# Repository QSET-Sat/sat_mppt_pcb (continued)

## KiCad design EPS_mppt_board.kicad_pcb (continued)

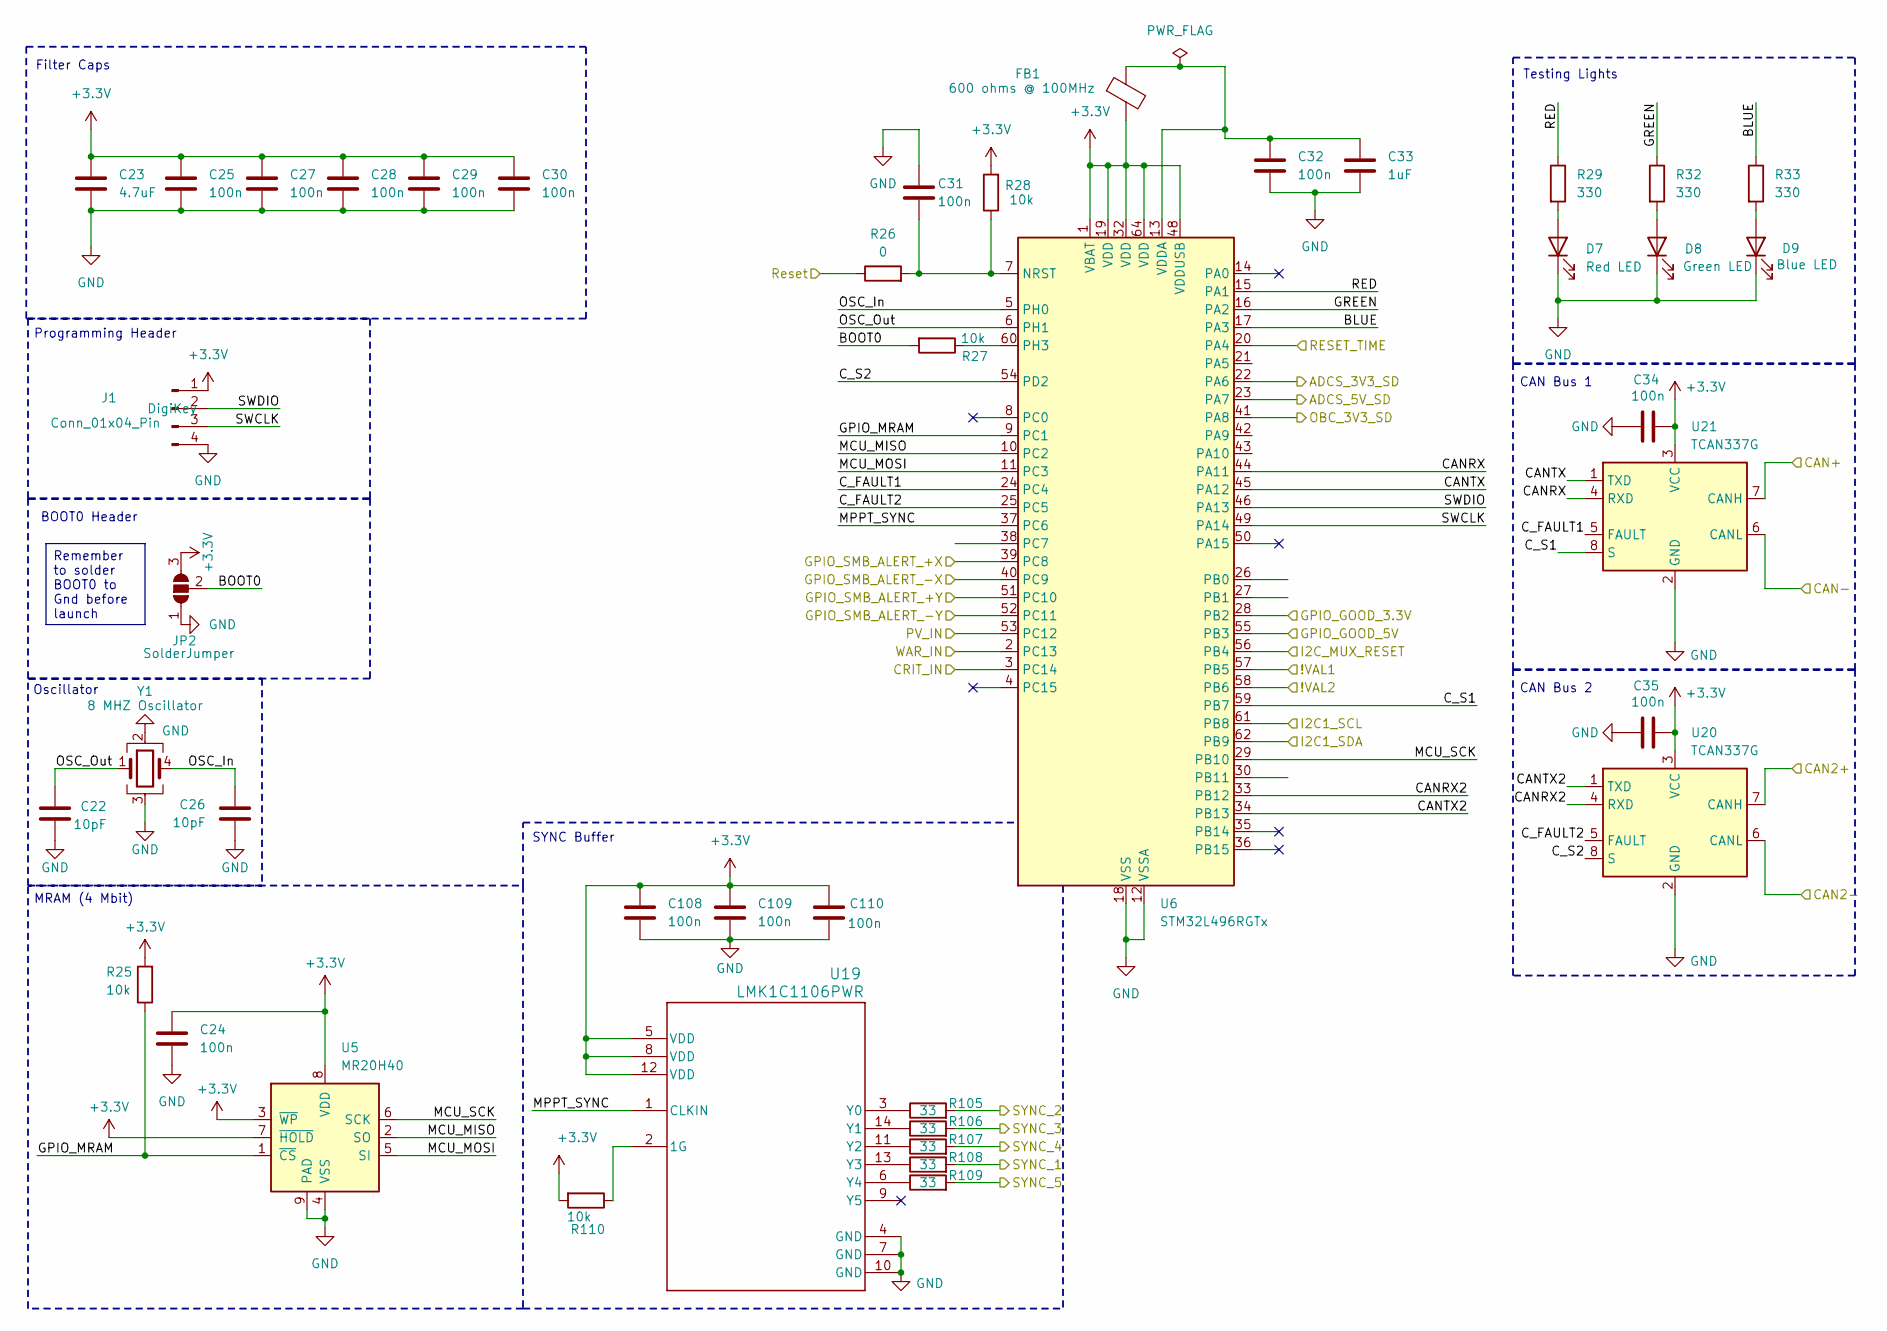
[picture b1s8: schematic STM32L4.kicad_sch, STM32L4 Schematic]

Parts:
C22, C26: 10pF; C_0603_1608Metric; MANUFACTURER_PART_NUMBER 06035C100K4T4A
C23: 4.7uF; C_0603_1608Metric; MANUFACTURER_PART_NUMBER CL10B475KQ8NQNC
C24, C25, C27, C28, C29, C30, C31, C32, C34, C35, C108, C109, C110: 100n; C_0603_1608Metric; MANUFACTURER_PART_NUMBER C0603X104K5RACTU
C33: 1uF; C_0603_1608Metric; MANUFACTURER_PART_NUMBER CL10B105KQ8NNNC
D7: Red LED; LED_0603_1608Metric; MANUFACTURER_PART_NUMBER 150060RS55040
D8: Green LED; LED_0603_1608Metric; MANUFACTURER_PART_NUMBER 150060VS55040
D9: Blue LED; LED_0603_1608Metric; MANUFACTURER_PART_NUMBER 150060BS55040
FB1: 600 ohms @ 100MHz; L_0603_1608Metric; MANUFACTURER_PART_NUMBER BLM18AG601SN1D
J1: Conn_01x04_Pin; JST_EH_B4B-EH-A_1x04_P2.50mm_Vertical
JP2: SolderJumper; SolderJumper-3_P1.3mm_Open_RoundedPad1.0x1.5mm_NumberLabels
R25, R27, R28: 10k; R_0805_2012Metric; MANUFACTURER_PART_NUMBER TNPW080510K0FEEA
R26: 0; R_0603_1608Metric; MANUFACTURER_PART_NUMBER MCT0603MZ0000ZP500
R29, R32, R33: 330; R_0603_1608Metric; MANUFACTURER_PART_NUMBER RG1608P-331-B-T5
R105, R106, R107, R108, R109: 33; R_0402_1005Metric
R110: 10k; R_0603_1608Metric
U5: MR20H40; DFN-8-1EP_6x5mm_P1.27mm_EP4x4mm
U6: STM32L496RGTx; LQFP-64_10x10mm_P0.5mm
U19: LMK1C1106PWR; PW0014A-IPC_B
U20, U21: TCAN337G; SOIC-8_3.9x4.9mm_P1.27mm
Y1: 8 MHZ Oscillator; Crystal_SMD_3225-4Pin_3.2x2.5mm

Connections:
+3.3V: C23.1, C24.2, C25.1, C27.1, C28.1, C29.1, C30.1, C34.2, C35.2, C108.1, C109.1, C110.1, FB1.2, J1.1, JP2.3 (B), R25.2, R28.2, R110.2, U5.3 (~WP), U5.7 (~HOLD), U5.8 (VDD), U6.1 (VBAT), U6.19 (VDD), U6.32 (VDD), U6.48 (VDDUSB), U6.64 (VDD), U19.5 (VDD), U19.8 (VDD), U19.12 (VDD), U20.3 (VCC), U21.3 (VCC); also elsewhere on the board
/3.3V and 5V Line/PGOOD1: U6.55 (PB3); also elsewhere on the board
/3.3V and 5V Line/PGOOD2: U6.28 (PB2); also elsewhere on the board
/3.3V and 5V Line/SYNC: R109.2; also elsewhere on the board
/Current Sensing and Fault Detection/ADCS_3V3_ShutDown: U6.22 (PA6); also elsewhere on the board
/Current Sensing and Fault Detection/ADCS_5V_ShutDown: U6.23 (PA7); also elsewhere on the board
/Current Sensing and Fault Detection/CRIT_INA3221: U6.3 (PC14); also elsewhere on the board
/Current Sensing and Fault Detection/OBC_3V3_ShutDown: U6.41 (PA8); also elsewhere on the board
/Current Sensing and Fault Detection/PV_INA3221: U6.53 (PC12); also elsewhere on the board
/Current Sensing and Fault Detection/SCL_INA3221: U6.61 (PB8); also elsewhere on the board
/Current Sensing and Fault Detection/SDA_INA3221: U6.62 (PB9); also elsewhere on the board
/Current Sensing and Fault Detection/WAR_INA3221: U6.2 (PC13); also elsewhere on the board
/EPS Logic/!VAL1: U6.57 (PB5); also elsewhere on the board
/EPS Logic/!VAL2: U6.58 (PB6); also elsewhere on the board
/External Watchdog IC/RESET_TIME: U6.20 (PA4); also elsewhere on the board
/External Watchdog IC/Reset: R26.1; also elsewhere on the board
/I2C Mux/I2C_Reset: U6.56 (PB4); also elsewhere on the board
/MPPT IC/!SMB_ALERT_+X: U6.39 (PC8); also elsewhere on the board
/MPPT IC/!SMB_ALERT_+Y: U6.51 (PC10); also elsewhere on the board
/MPPT IC/!SMB_ALERT_-X: U6.40 (PC9); also elsewhere on the board
/MPPT IC/!SMB_ALERT_-Y: U6.52 (PC11); also elsewhere on the board
/MPPT IC/MPPT_SYNC_1.5MHz_1: R108.2; also elsewhere on the board
/MPPT IC/MPPT_SYNC_1.5MHz_2: R105.2; also elsewhere on the board
/MPPT IC/MPPT_SYNC_1.5MHz_3: R106.2; also elsewhere on the board
/MPPT IC/MPPT_SYNC_1.5MHz_4: R107.2; also elsewhere on the board
/PC104/CAN2+: U20.7 (CANH); also elsewhere on the board
/PC104/CAN2-: U20.6 (CANL); also elsewhere on the board
/PC104/CAN+: U21.7 (CANH); also elsewhere on the board
/PC104/CAN-: U21.6 (CANL); also elsewhere on the board
/STM32L4/BLUE: R33.1, U6.17 (PA3)
/STM32L4/BOOT0: JP2.2 (C), R27.2
/STM32L4/CANRX: U6.44 (PA11), U21.4 (RXD)
/STM32L4/CANRX2: U6.33 (PB12), U20.4 (RXD)
/STM32L4/CANTX: U6.45 (PA12), U21.1 (TXD)
/STM32L4/CANTX2: U6.34 (PB13), U20.1 (TXD)
/STM32L4/C_FAULT1: U6.24 (PC4), U21.5 (FAULT)
/STM32L4/C_FAULT2: U6.25 (PC5), U20.5 (FAULT)
/STM32L4/C_S1: U6.59 (PB7), U21.8 (S)
/STM32L4/C_S2: U6.54 (PD2), U20.8 (S)
/STM32L4/GPIO_MRAM: R25.1, U5.1 (~CS), U6.9 (PC1)
/STM32L4/GREEN: R32.1, U6.16 (PA2)
/STM32L4/MCU_MISO: U5.2 (SO), U6.10 (PC2)
/STM32L4/MCU_MOSI: U5.5 (SI), U6.11 (PC3)
/STM32L4/MCU_SCK: U5.6 (SCK), U6.29 (PB10)
/STM32L4/MPPT_SYNC: U6.37 (PC6), U19.1 (CLKIN)
/STM32L4/OSC_In: C26.1, U6.5 (PH0), Y1.4
/STM32L4/OSC_Out: C22.1, U6.6 (PH1), Y1.1
/STM32L4/RED: R29.1, U6.15 (PA1)
/STM32L4/SWCLK: J1.3, U6.49 (PA14)
/STM32L4/SWDIO: J1.2, U6.46 (PA13)
unnamed: D7.2 (A), R29.2
unnamed: D8.2 (A), R32.2
unnamed: D9.2 (A), R33.2
unnamed: C31.2, R26.2, R28.1, U6.7 (NRST)
unnamed: R27.1, U6.60 (PH3)
unnamed: C32.1, C33.1, FB1.1, U6.13 (VDDA)
unnamed: R110.1, U19.2 (1G)
unnamed: R105.1, U19.3 (Y0)
unnamed: R106.1, U19.14 (Y1)
unnamed: R107.1, U19.11 (Y2)
unnamed: R108.1, U19.13 (Y3)
unnamed: R109.1, U19.6 (Y4)

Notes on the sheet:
SYNC Buffer
CAN Bus 1
Oscillator
Testing Lights
BOOT0 Header
CAN Bus 2
Filter Caps
Programming Header
MRAM (4 Mbit)
Remember to solder BOOT0 to Gnd before launch

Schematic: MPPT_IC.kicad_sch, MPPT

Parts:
C17, C18, C19, C20: 47 uF; CP_EIA-7343-43_Kemet-X; MANUFACTURER_PART_NUMBER T54EE476M050ESA100
C21: 10 uF; C_1206_3216Metric; MANUFACTURER_PART_NUMBER CNA5L1X7R1H106K160AE
D3, D4, D5, D6: D_Schottky; D_SOD-128; MANUFACTURER_PART_NUMBER PMEG10020AELP-QX

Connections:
/EPS Logic/OR'd_VOUT: C21.2, D3.1 (K), D4.1 (K), D5.1 (K), D6.1 (K); also elsewhere on the board
/MPPT IC/+X_MPPT/VOUT: D3.2 (A); also elsewhere on the board
/MPPT IC/+Y_MPPT/VOUT: D5.2 (A); also elsewhere on the board
/MPPT IC/-X_MPPT/VOUT: D4.2 (A); also elsewhere on the board
/MPPT IC/-Y_MPPT/VOUT: D6.2 (A); also elsewhere on the board
BATT_1: C18.1, C20.1; also elsewhere on the board
BATT_2: C17.1, C19.1; also elsewhere on the board

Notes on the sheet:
+Y MPPT
-X MPPT
+X MPPT
-Y MPPT
Notes: -!SMB_ALERT will be tied to a External Interrupt Line (EXTI) on the MCU which will be triggered by a falling edge - Assumptions made when calculating inductor val: 15V solar input, 8.4V battery, 1.2A max charge limit 10uH (max I= 3A) (<30m ohms)

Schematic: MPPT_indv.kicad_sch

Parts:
C64, C65, C66: 47 uF; CP_EIA-7343-43_Kemet-X; MANUFACTURER_PART_NUMBER T54EE476M050ESA100
C67, C69: 100n; C_0402_1005Metric; MANUFACTURER_PART_NUMBER AVX, 04025C104KAT2A
C68: 22nF; C_0402_1005Metric; MANUFACTURER_PART_NUMBER 0402YC223KAT2A
C70: 4.7 uF; C_0603_1608Metric; MANUFACTURER_PART_NUMBER CL10B475KQ8NQNC
C71: 100n; R_0402_1005Metric; MANUFACTURER_PART_NUMBER AVX, 04025C104KAT2A
C72, C74: 10 uF; C_1206_3216Metric; MANUFACTURER_PART_NUMBER CNA5L1X7R1H106K160AE
C73: 1 uF; C_0603_1608Metric; MANUFACTURER_PART_NUMBER CL10B105KQ8NNNC
D10: SMAJ22A; D_SMA
L3: 4.7uH; XAL6060472MEC; MANUFACTURER_PART_NUMBER Coilcraft XAL6060-472MEC
Q8, Q9: Q_NMOS; IFX-PG-TSDSON-8-44-V; MANUFACTURER_PART_NUMBER IAUZN04S7L046ATMA1
R73: 2.5; R_1206_3216Metric; MANUFACTURER_PART_NUMBER CRCW12062R49FKEAHP
R74, R75: 4.7k; R_0603_1608Metric; MANUFACTURER_PART_NUMBER MCT0603MC4701FP500
R76: 10k; R_0603_1608Metric
R77, R79: 10m; R_0612_1632Metric; MANUFACTURER_PART_NUMBER PRL1632-R010-F-T1
R78: 63.4k; R_0603_1608Metric
R80: 10k; R_0805_2012Metric; MANUFACTURER_PART_NUMBER TNPW080510K0FEEA
U15: LTC4162IUFD-LADM_PBF; QFN-28-1EP_4x5mm_P0.5mm_EP2.65x3.65mm_ThermalVias; PARTREV A

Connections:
+3.3V: R74.1, R75.1, R76.1, U15.15 (DVCC); also elsewhere on the board
/I2C Mux/SCL_+X: R75.2, U15.13 (SCL); also elsewhere on the board
/I2C Mux/SDA_+X: R74.2, U15.14 (SDA); also elsewhere on the board
/MPPT IC/!SMB_ALERT_+X: R76.2, U15.12 (~SMBALERT); also elsewhere on the board
/MPPT IC/+X_MPPT/IntVCC_+X: C70.1, U15.2 (INTVCC), U15.18 (CELLS1)
/MPPT IC/+X_MPPT/VCC2P5_+X: C73.1, U15.8 (VCC2P5), U15.17 (CELLS0)
/MPPT IC/+X_MPPT/VOUT: C69.1, C74.1, Q9.5 (D), Q9.6 (D), Q9.7 (D), Q9.8 (D), R77.2, U15.3 (VOUTA), U15.4 (CLN), U15.27 (VOUT), U15.28 (VOUT__1); also elsewhere on the board
/MPPT IC/BattSen2: C71.1, U15.19 (BATSENS+); also elsewhere on the board
/MPPT IC/MPPT_SYNC_1.5MHz_1: U15.16 (SYNC); also elsewhere on the board
/MPPT IC/SOLAR_+X: C67.1, D10.1 (A1), Q8.1 (S), Q8.2, Q8.3 (S), R73.1, U15.7 (VIN); also elsewhere on the board
/T1: R80.2, U15.10 (NTC); also elsewhere on the board
BATT_1: C72.2, R79.2, U15.20 (CSN); also elsewhere on the board
unnamed: C64.1, C65.1, C66.1, R73.2
unnamed: Q8.4 (G), U15.6 (INFET)
unnamed: Q9.4 (G), U15.22 (BATFET)
unnamed: C68.1, U15.1 (BOOST)
unnamed: Q8.5 (D), Q8.6 (D), Q8.7 (D), Q8.8 (D), R77.1, U15.5 (CLP)
unnamed: L3.2, Q9.1 (S), Q9.2, Q9.3 (S), R79.1, U15.21 (CSP)
unnamed: R80.1, U15.9 (NTCBIAS)
unnamed: R78.1, U15.11 (RT)
unnamed: C68.2, L3.1, U15.25 (SW), U15.26 (SW__1)

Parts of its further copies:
C75, C76, C77, C86, C87, C88, C97, C98, C99: 47 uF; CP_EIA-7343-43_Kemet-X; MANUFACTURER_PART_NUMBER T54EE476M050ESA100
C78, C80, C89, C91, C100, C102: 100n; C_0402_1005Metric; MANUFACTURER_PART_NUMBER AVX, 04025C104KAT2A
C79, C90, C101: 22nF; C_0402_1005Metric; MANUFACTURER_PART_NUMBER 0402YC223KAT2A
C81, C92, C103: 4.7 uF; C_0603_1608Metric; MANUFACTURER_PART_NUMBER CL10B475KQ8NQNC
C82, C93, C104: 100n; R_0402_1005Metric; MANUFACTURER_PART_NUMBER AVX, 04025C104KAT2A
C83, C85, C94, C96, C105, C107: 10 uF; C_1206_3216Metric; MANUFACTURER_PART_NUMBER CNA5L1X7R1H106K160AE
C84, C95, C106: 1 uF; C_0603_1608Metric; MANUFACTURER_PART_NUMBER CL10B105KQ8NNNC
D11, D12, D13: SMAJ22A; D_SMA
L4, L5, L6: 4.7uH; XAL6060472MEC; MANUFACTURER_PART_NUMBER Coilcraft XAL6060-472MEC
Q10, Q11, Q12, Q13, Q14, Q15: Q_NMOS; IFX-PG-TSDSON-8-44-V; MANUFACTURER_PART_NUMBER IAUZN04S7L046ATMA1
R81, R89, R97: 2.5; R_1206_3216Metric; MANUFACTURER_PART_NUMBER CRCW12062R49FKEAHP
R82, R83, R90, R91, R98, R99: 4.7k; R_0603_1608Metric; MANUFACTURER_PART_NUMBER MCT0603MC4701FP500
R84, R92, R100: 10k; R_0603_1608Metric
R85, R87, R93, R95, R101, R103: 10m; R_0612_1632Metric; MANUFACTURER_PART_NUMBER PRL1632-R010-F-T1
R86, R94, R102: 63.4k; R_0603_1608Metric
R88, R96, R104: 10k; R_0805_2012Metric; MANUFACTURER_PART_NUMBER TNPW080510K0FEEA
U16, U17, U18: LTC4162IUFD-LADM_PBF; QFN-28-1EP_4x5mm_P0.5mm_EP2.65x3.65mm_ThermalVias; PARTREV A

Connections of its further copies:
+3.3V: R82.1, R83.1, R84.1, R90.1, R91.1, R92.1, R98.1, R99.1, R100.1, U16.15 (DVCC), U17.15 (DVCC), U18.15 (DVCC); also elsewhere on the board
/I2C Mux/SCL_+Y: R83.2, U16.13 (SCL); also elsewhere on the board
/I2C Mux/SCL_-X: R91.2, U17.13 (SCL); also elsewhere on the board
/I2C Mux/SCL_-Y: R99.2, U18.13 (SCL); also elsewhere on the board
/I2C Mux/SDA_+Y: R82.2, U16.14 (SDA); also elsewhere on the board
/I2C Mux/SDA_-X: R90.2, U17.14 (SDA); also elsewhere on the board
/I2C Mux/SDA_-Y: R98.2, U18.14 (SDA); also elsewhere on the board
/MPPT IC/!SMB_ALERT_+Y: R84.2, U16.12 (~SMBALERT); also elsewhere on the board
/MPPT IC/!SMB_ALERT_-X: R92.2, U17.12 (~SMBALERT); also elsewhere on the board
/MPPT IC/!SMB_ALERT_-Y: R100.2, U18.12 (~SMBALERT); also elsewhere on the board
/MPPT IC/+Y_MPPT/IntVCC_+X: C81.1, U16.2 (INTVCC), U16.18 (CELLS1)
/MPPT IC/+Y_MPPT/VCC2P5_+X: C84.1, U16.8 (VCC2P5), U16.17 (CELLS0)
/MPPT IC/+Y_MPPT/VOUT: C80.1, C85.1, Q11.5 (D), Q11.6 (D), Q11.7 (D), Q11.8 (D), R85.2, U16.3 (VOUTA), U16.4 (CLN), U16.27 (VOUT), U16.28 (VOUT__1); also elsewhere on the board
/MPPT IC/-X_MPPT/IntVCC_+X: C92.1, U17.2 (INTVCC), U17.18 (CELLS1)
/MPPT IC/-X_MPPT/VCC2P5_+X: C95.1, U17.8 (VCC2P5), U17.17 (CELLS0)
/MPPT IC/-X_MPPT/VOUT: C91.1, C96.1, Q13.5 (D), Q13.6 (D), Q13.7 (D), Q13.8 (D), R93.2, U17.3 (VOUTA), U17.4 (CLN), U17.27 (VOUT), U17.28 (VOUT__1); also elsewhere on the board
/MPPT IC/-Y_MPPT/IntVCC_+X: C103.1, U18.2 (INTVCC), U18.18 (CELLS1)
/MPPT IC/-Y_MPPT/VCC2P5_+X: C106.1, U18.8 (VCC2P5), U18.17 (CELLS0)
/MPPT IC/-Y_MPPT/VOUT: C102.1, C107.1, Q15.5 (D), Q15.6 (D), Q15.7 (D), Q15.8 (D), R101.2, U18.3 (VOUTA), U18.4 (CLN), U18.27 (VOUT), U18.28 (VOUT__1); also elsewhere on the board
/MPPT IC/BattSen1: C93.1, C104.1, U17.19 (BATSENS+), U18.19 (BATSENS+); also elsewhere on the board
/MPPT IC/BattSen2: C82.1, U16.19 (BATSENS+); also elsewhere on the board
/MPPT IC/MPPT_SYNC_1.5MHz_2: U17.16 (SYNC); also elsewhere on the board
/MPPT IC/MPPT_SYNC_1.5MHz_3: U16.16 (SYNC); also elsewhere on the board
/MPPT IC/MPPT_SYNC_1.5MHz_4: U18.16 (SYNC); also elsewhere on the board
/MPPT IC/SOLAR_+Y: C78.1, D11.1 (A1), Q10.1 (S), Q10.2, Q10.3 (S), R81.1, U16.7 (VIN); also elsewhere on the board
/MPPT IC/SOLAR_-X: C89.1, D12.1 (A1), Q12.1 (S), Q12.2, Q12.3 (S), R89.1, U17.7 (VIN); also elsewhere on the board
/MPPT IC/SOLAR_-Y: C100.1, D13.1 (A1), Q14.1 (S), Q14.2, Q14.3 (S), R97.1, U18.7 (VIN); also elsewhere on the board
/T2: R96.2, U17.10 (NTC); also elsewhere on the board
/T3: R88.2, U16.10 (NTC); also elsewhere on the board
/T4: R104.2, U18.10 (NTC); also elsewhere on the board
BATT_1: C83.2, R87.2, U16.20 (CSN); also elsewhere on the board
BATT_2: C94.2, C105.2, R95.2, R103.2, U17.20 (CSN), U18.20 (CSN); also elsewhere on the board
unnamed: C75.1, C76.1, C77.1, R81.2
unnamed: C86.1, C87.1, C88.1, R89.2
unnamed: C97.1, C98.1, C99.1, R97.2
unnamed: Q10.4 (G), U16.6 (INFET)
unnamed: Q11.4 (G), U16.22 (BATFET)
unnamed: Q12.4 (G), U17.6 (INFET)
unnamed: Q13.4 (G), U17.22 (BATFET)
unnamed: Q14.4 (G), U18.6 (INFET)
unnamed: Q15.4 (G), U18.22 (BATFET)
unnamed: C79.1, U16.1 (BOOST)
unnamed: Q10.5 (D), Q10.6 (D), Q10.7 (D), Q10.8 (D), R85.1, U16.5 (CLP)
unnamed: L4.2, Q11.1 (S), Q11.2, Q11.3 (S), R87.1, U16.21 (CSP)
unnamed: R88.1, U16.9 (NTCBIAS)
unnamed: R86.1, U16.11 (RT)
unnamed: C79.2, L4.1, U16.25 (SW), U16.26 (SW__1)
unnamed: C90.1, U17.1 (BOOST)
unnamed: Q12.5 (D), Q12.6 (D), Q12.7 (D), Q12.8 (D), R93.1, U17.5 (CLP)
unnamed: L5.2, Q13.1 (S), Q13.2, Q13.3 (S), R95.1, U17.21 (CSP)
unnamed: R96.1, U17.9 (NTCBIAS)
unnamed: R94.1, U17.11 (RT)
unnamed: C90.2, L5.1, U17.25 (SW), U17.26 (SW__1)
unnamed: C101.1, U18.1 (BOOST)
unnamed: Q14.5 (D), Q14.6 (D), Q14.7 (D), Q14.8 (D), R101.1, U18.5 (CLP)
unnamed: L6.2, Q15.1 (S), Q15.2, Q15.3 (S), R103.1, U18.21 (CSP)
unnamed: R104.1, U18.9 (NTCBIAS)
unnamed: R102.1, U18.11 (RT)
unnamed: C101.2, L6.1, U18.25 (SW), U18.26 (SW__1)

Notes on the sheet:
Maximum Power Point Tracker and Battery Charger
The NTC Pin Will be on the Battery Board for measuring battery Temp
Make Sure R here is precise and has a low temp coeff
have a TIM output at 1.5MHz from one pin to all SYNCs and keep all 63.4k ohm resistors. This will sync all of their freqs and negate the risk of beat freqs
Some GND notes: PGND (Pins 23,24): Power ground pins. These pins should be connected to a copper pour that forms the return for the V OUT bypass capacitor on the top layer of the printed circuit board. AGND (Exposed PAD, Pin 29): Analog ground pin. This is the ground pin used to return all of the a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

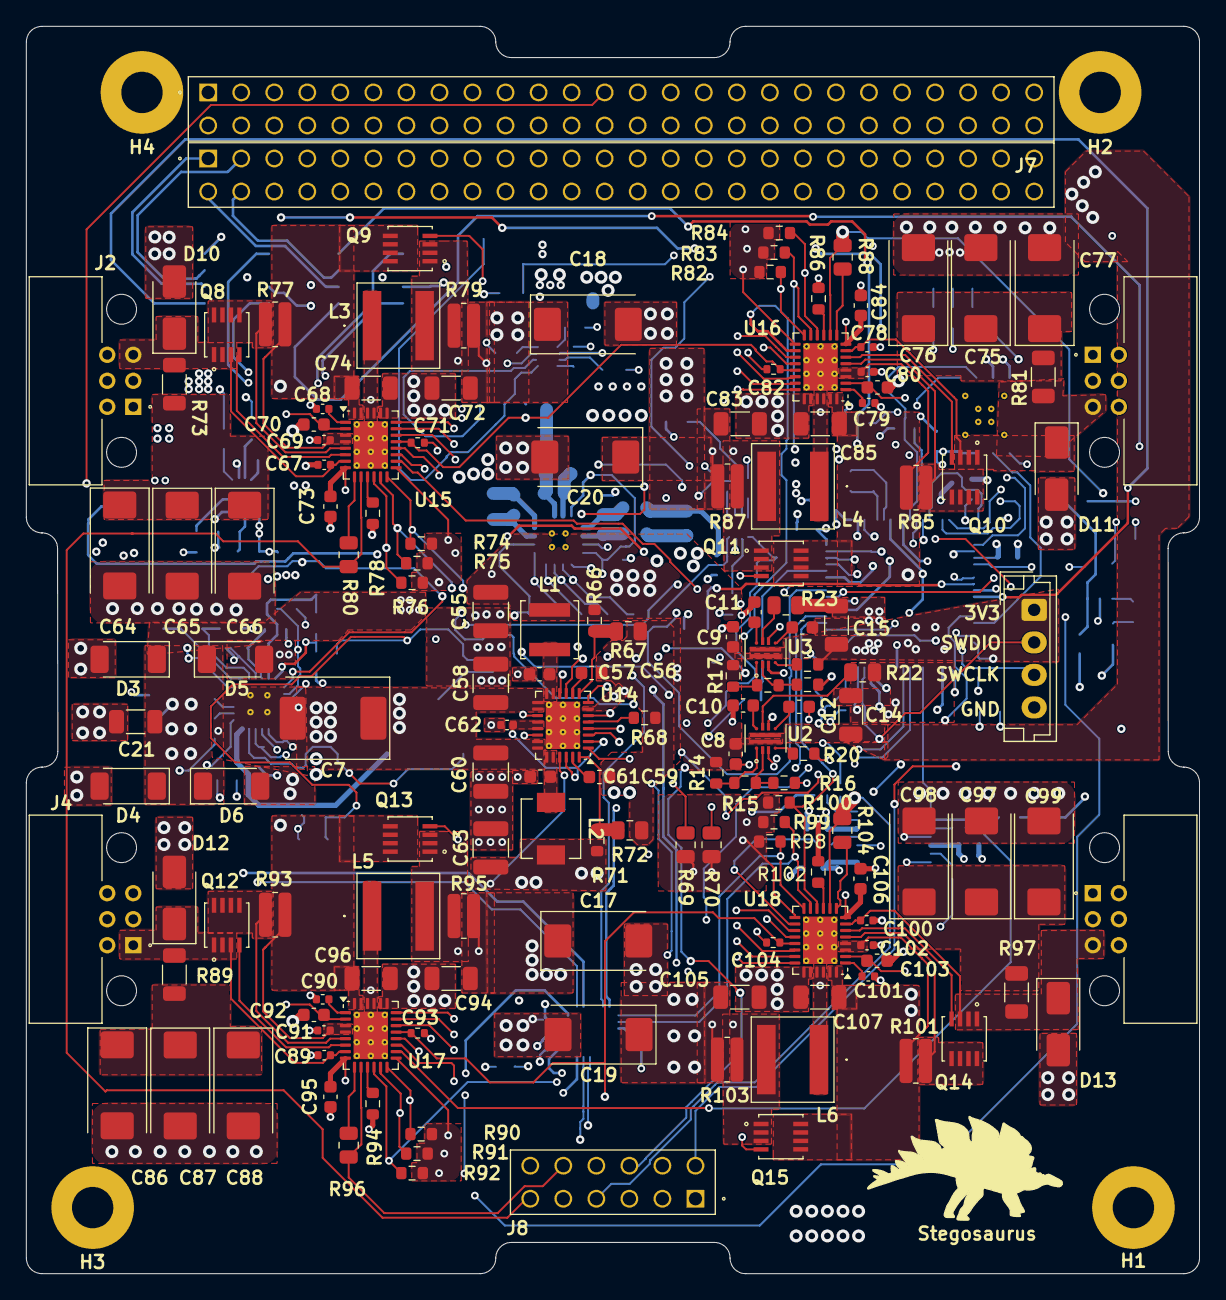
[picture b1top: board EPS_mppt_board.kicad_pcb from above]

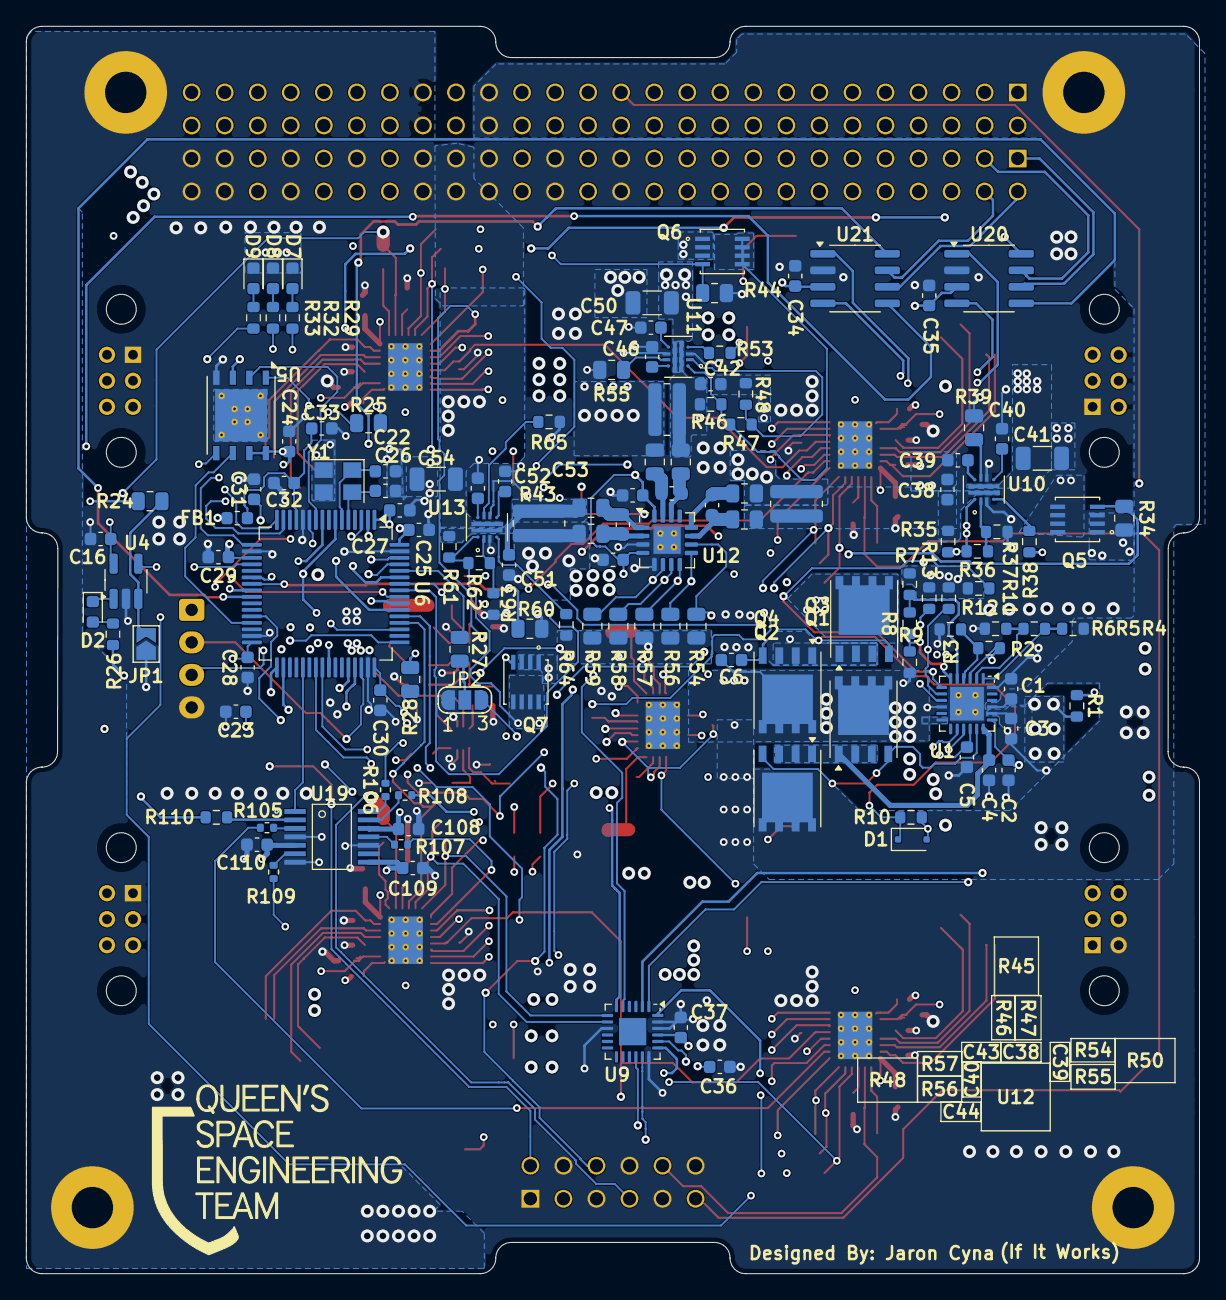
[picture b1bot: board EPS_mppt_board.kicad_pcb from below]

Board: 6 copper layers, 90.2 x 95.9 mm, 287 parts (130 on the bottom side), 203 nets.
